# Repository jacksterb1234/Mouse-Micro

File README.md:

# Mouse-Micro — Custom Ergonomic Gaming Mouse

A fully custom gaming mouse built from scratch — from clay hand modeling and photogrammetry all the way to a custom KiCad PCB. Designed to prevent repetitive strain injuries during extended use while delivering high-precision tracking.

## Features

- **Ergonomic form** designed from a clay hand model, digitized via photogrammetry (Meshroom), refined in Fusion360 using surface modeling
- **Custom PCB** designed in KiCad with:
  - **Arduino Pro Micro** microcontroller
  - **PMW3389** high-precision optical sensor (SPI communication)
  - Left click, right click, forward, back, scroll wheel (rotation + press), adjustable DPI
- **USB-Micro** connection
- Uses the **AdvMouse** library for low-latency HID reporting
- Compatible with any device — no drivers required
- Integrated mounting for buttons, PCB, and sensor alignment

## Repository Structure

```
Mouse-Micro/
├── CAD/                     # Fusion360 mouse body surface model
├── Code/PMW3389DM_Mouse/    # Arduino firmware (PMW3389 + AdvMouse)
├── D2F-01/                  # Omron switch footprints
├── PMW3360/                 # PMW3360 sensor footprints (alternate)
├── PMW3389/                 # PMW3389 sensor footprints
├── ProMicroKiCad-master/   # Pro Micro KiCad library
├── ul_EC10E1220501/         # Scroll encoder footprint
├── Mouse-backups/          # KiCad schematic backups
├── Output/                  # Gerber and production output files
├── Mouse.kicad_pro          # KiCad project file
└── Mouse-Shaft.SLDPRT      # SolidWorks shaft model
```

## Tools Used

- **Meshroom** — Photogrammetry mesh generation from clay model
- **Fusion360** — Surface modeling and CAD refinement
- **KiCad** — Schematic capture and PCB layout
- **Arduino IDE** — Firmware development
- **SolidWorks** — Mechanical shaft design

## Key Components

| Component | Function |
|-----------|----------|
| Arduino Pro Micro | USB HID microcontroller |
| PMW3389 | High-precision optical sensor (up to 16000 DPI) |
| Omron D2F-01 | Tactile click switches |
| EC10E1220501 | Scroll wheel rotary encoder |

## Author

**Jackson Barber** — [github.com/jacksterb1234](https://github.com/jacksterb1234)

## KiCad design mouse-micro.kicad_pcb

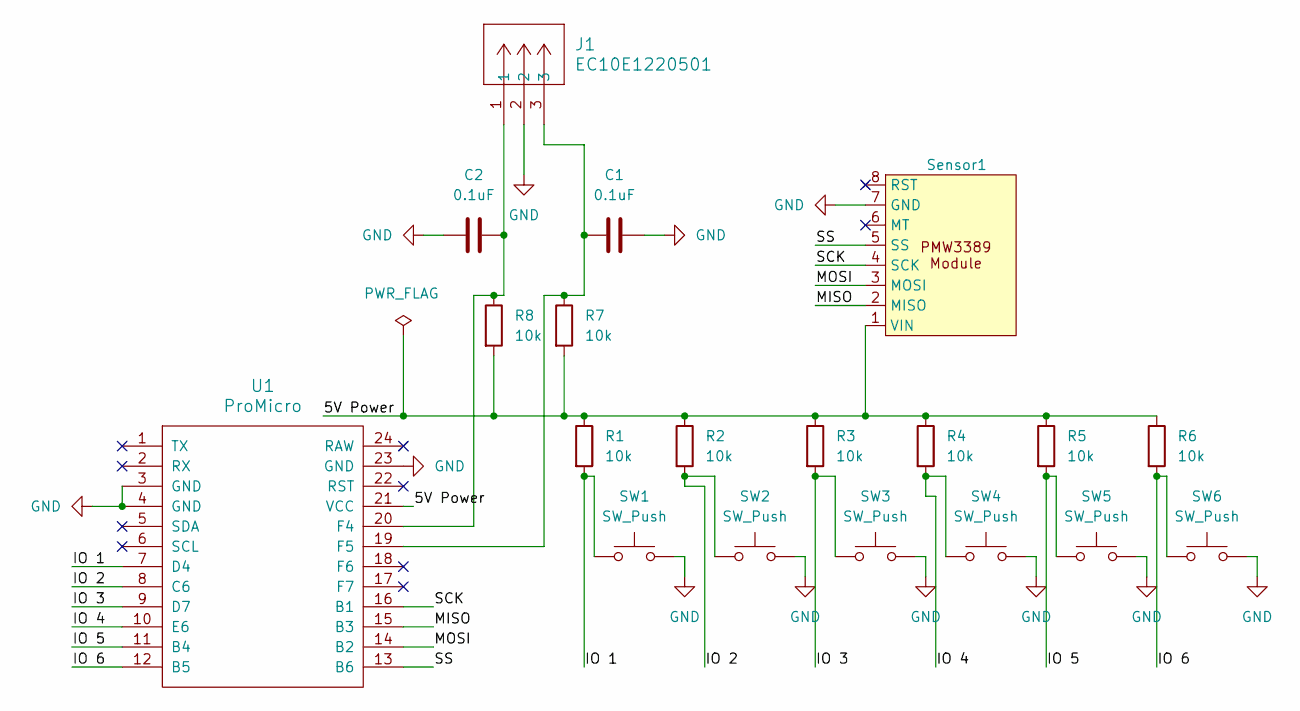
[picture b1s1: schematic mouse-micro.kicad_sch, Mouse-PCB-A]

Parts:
C1, C2: 0.1uF; C_Disc_D5.0mm_W2.5mm_P2.50mm
J1: EC10E1220501; CONN03_EC10E_9P8X6P1_ALPS
R1, R2, R3, R4, R5, R6, R7, R8: 10k; R_Axial_DIN0207_L6.3mm_D2.5mm_P7.62mm_Horizontal
SW1, SW2, SW3, SW4, SW5, SW6: SW_Push; SW_D2F-01F
Sensor1: PMW3389_Module
U1: ProMicro

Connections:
/5V Power: R1.1, R2.1, R3.1, R4.1, R5.1, R6.1, R7.2, R8.2, Sensor1.1 (VIN), U1.21 (VCC)
/IO 1: R1.2, SW1.1, U1.7 (D4)
/IO 2: R2.2, SW2.1, U1.8 (C6)
/IO 3: R3.2, SW3.1, U1.9 (D7)
/IO 4: R4.2, SW4.1, U1.10 (E6)
/IO 5: R5.2, SW5.1, U1.11 (B4)
/IO 6: R6.2, SW6.1, U1.12 (B5)
/MISO: Sensor1.2 (MISO), U1.15 (B3)
/MOSI: Sensor1.3 (MOSI), U1.14 (B2)
/SCK: Sensor1.4 (SCK), U1.16 (B1)
/SS: Sensor1.5 (SS), U1.13 (B6)
GND: C1.2, C2.1, J1.2, SW1.2, SW2.2, SW3.2, SW4.2, SW5.2, SW6.2, Sensor1.7 (GND), U1.3 (GND), U1.4 (GND), U1.23 (GND)
unnamed: C2.2, J1.1, R8.1, U1.20 (F4)
unnamed: C1.1, J1.3, R7.1, U1.19 (F5)

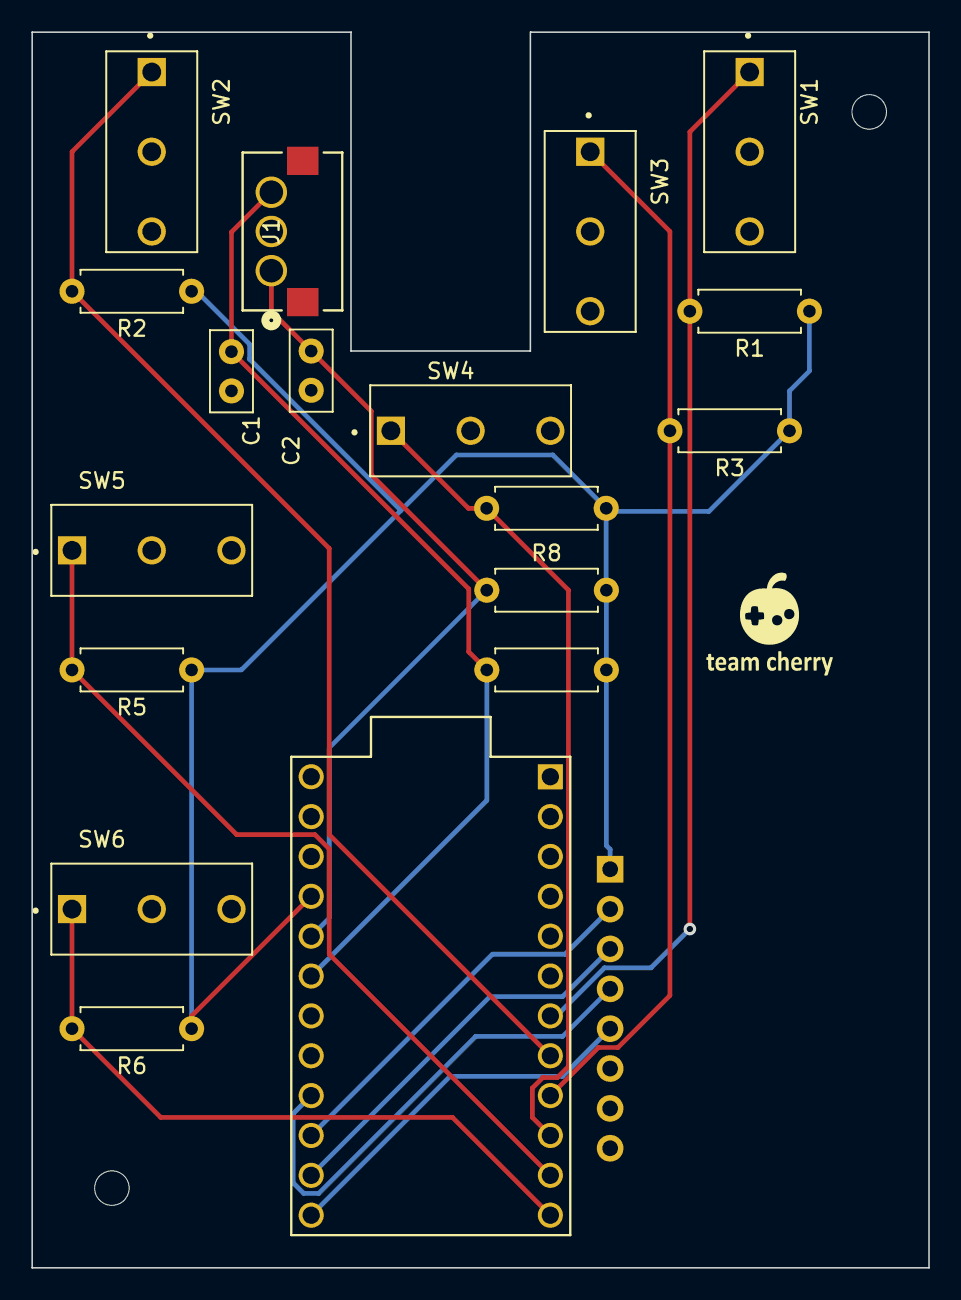
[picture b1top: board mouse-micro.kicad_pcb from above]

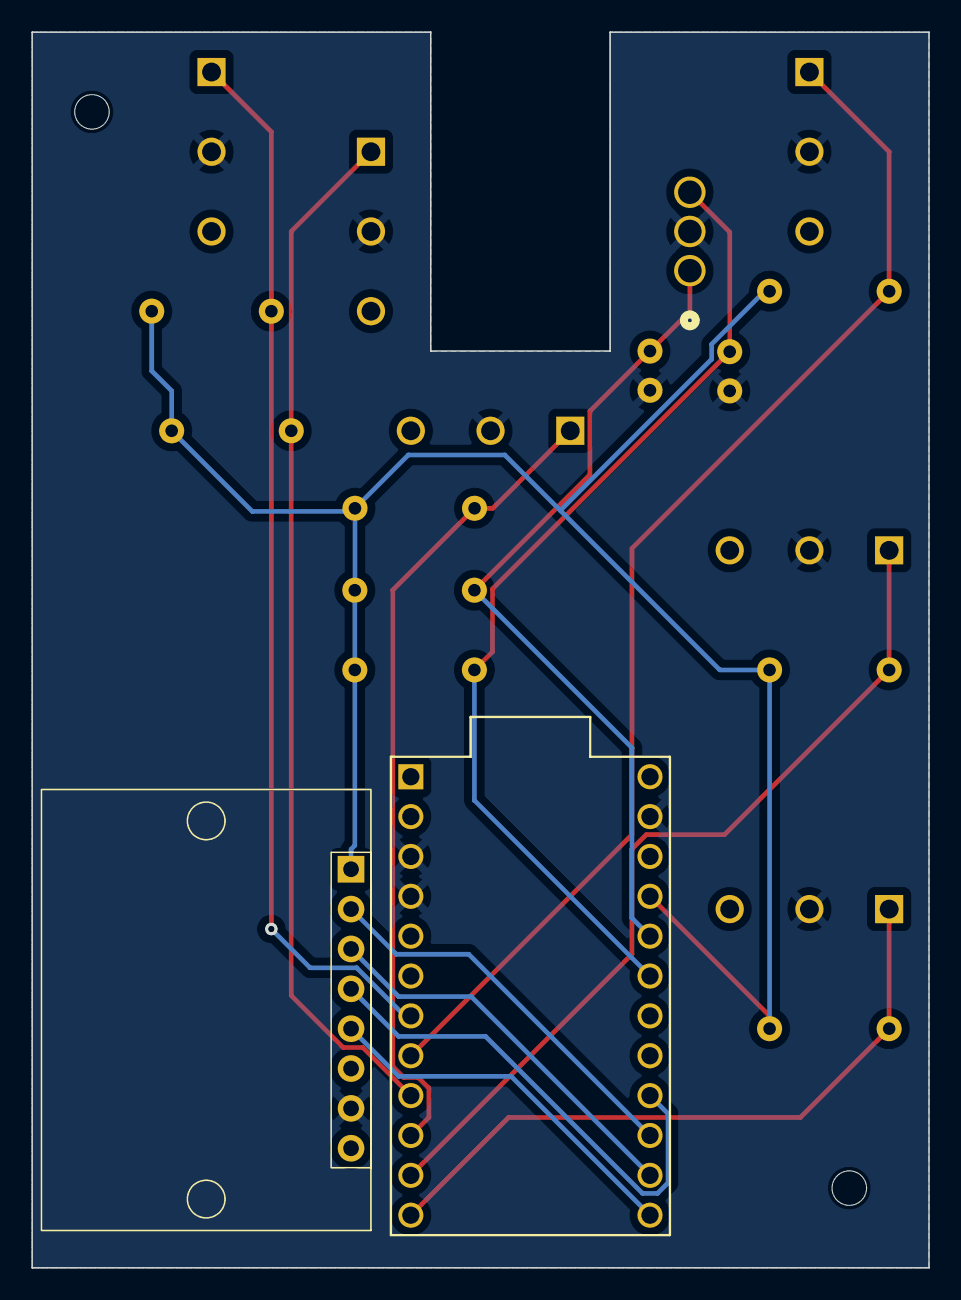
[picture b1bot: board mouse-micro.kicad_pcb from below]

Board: 2 copper layers, 57.2 x 78.7 mm, 19 parts (2 on the bottom side), 14 nets.

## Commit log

2026-01-29 Added code, modifed side buttons
2026-02-07 Updated Code
2026-02-10 Modified CAD to ensure buttons don't contact sensor, code works!
2026-05-30 Add README
    Added detailed project description, features, repository structure, tools used, key components, and author information.
